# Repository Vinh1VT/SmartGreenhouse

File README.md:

# Mr Gardener - Serre Connectée

Ce dépôt contient les sources utilisée dans le projet Mr. Gardener, réalisé en 2026 pour la formation Electronique-Informatique d'année 4 à Polytech Sorbonne.

Ce document n'est qu'une courte description du projet, une documentation plus détaillé peut être trouvée [ici](https://github.com/Vinh1VT/SmartGreenhouse/blob/main/Mr.Gardener%20-%20SmartGreenHouse%20-%20User%20Guide.pdf)

##  Objectifs du projet

L'objectif principal est de concevoir un système autonome de mesures et de commandes pour la serre de l'école, sur le campus St Cyr l'école.
Le systême à donc comme caractéristique : 

- **Mesures Environnementale** : Acquisition de données environnementales (Humidité, température, luminosité...) pour la serre et son puits canadien
- **Basse Consommation** : Le projet fonctionne quasi entièrement sur batterie, et grâce à un rechargement par panneau solaire est en permanence autonome
- **IA Embarquée** : Proof of concept d'une détection locale de panne du ventilateur de la serre, via une IA de classification Edge Impulse
- **Collecte et visualisation des données** : Collecte, traitement et visualisation des données, via The Things Network, InfluxDB et Grafana
- **Contrôle du ventilateur** : Prototype d'une contrôleur I2C pour le ventilateur du puits canadien de la serre. Va être remplacé par un système plus robuste

##  Structure du dépôt

Les dossiers de ce dépôt contiennent les élément suivants :

*  **`Iot_PCB/`** : Projets KiCad (schémas et routages) pour la carte mère et les contrôleurs de ventilateurs
*  **`code_esp32_WROOM_32E/`** : Firmware principal (ESP32) gérant la lecture des capteurs, la logique de commande et la connectivité LoRa
*  **`nano_AI/`** : Modèles d'intelligence artificielle et code d'inférence (Edge Impulse) tournant sur l'Arduino Nano
*  **`Server/`** : Dashboard Grafana, Script Python de liaison TTN<->InfluxDB et Parser TTN

## Auteurs : 
- Vinh VO TUAN
- Fallou CORDELETTE
- Quentin LE VOURC'H
- Yanis RAHOUI
- Taha OUERFILI

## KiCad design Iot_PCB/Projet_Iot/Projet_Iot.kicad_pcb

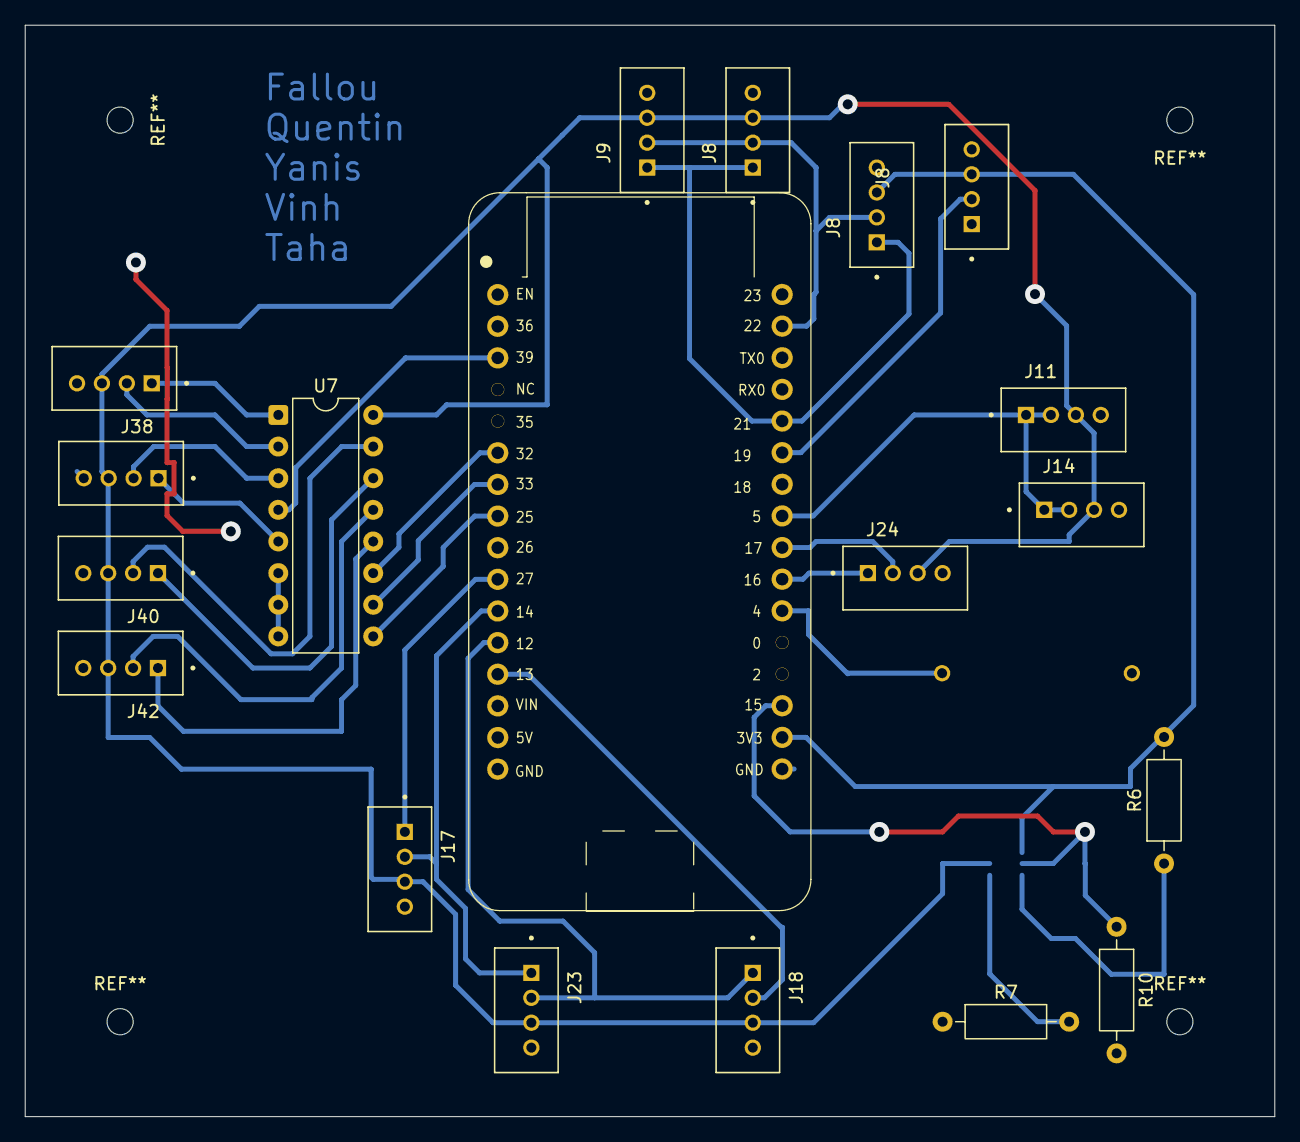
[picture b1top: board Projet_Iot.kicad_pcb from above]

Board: 2 copper layers, 100.3 x 87.6 mm, 20 parts (1 on the bottom side), 28 nets.

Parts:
J8, J8#2, J8#3, J9, J11, J14, J17, J18, J23, J24, J36, J38, J40, J42: 110990030; SEEED_110990030
R6: 1000; R_Axial_DIN0207_L6.3mm_D2.5mm_P10.16mm_Horizontal
R7: 100; R_Axial_DIN0207_L6.3mm_D2.5mm_P10.16mm_Horizontal
R10: 4700; R_Axial_DIN0207_L6.3mm_D2.5mm_P10.16mm_Horizontal
U6: uPesy_ESP32_Wroom_Low_Power_DevKit
U7: mx8v1_74LS151; DIP-16_W7.62mm
U11: FDC6326L; SOT95P280X110-6N

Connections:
/1_Wire: J11.1, J11.2, J14.1, J14.2, U6.24 (GPIO5)
/3v3: J8#3.3, J9.3, J11.3, J14.3, J17.3, J18.3, J23.3, J24.3, J36.3, J38.3, J40.3, J42.3, U7.16 (VCC), U11.2 (VOUT,C1_2)
/3v3_ESP: J8.3, J8#2.3, R6.2, U6.31 (3V3), U11.4 (VIN,R1)
/ADC1_S0: U6.6 (GPIO32), U7.11 (S0)
/ADC1_S1: U6.7 (GPIO33), U7.10 (S1)
/ADC1_S2: U6.8 (GPIO25), U7.9 (S2)
/ADC2: U6.3 (GPIO39), U7.4 (I0)
/Enable_LS: R10.1, U6.30 (GPIO15), U11.5 (ON/OFF)
/GND: J8.4, J8#2.4, J8#3.4, J9.4, J11.4, J14.4, J17.4, J18.4, J23.4, J24.4, J36.4, J38.4, J40.4, J42.4, R7.1, R10.2, U6.32 (GND), U7.6 (~Z), U7.7 (~E), U7.8 (GND)
/Grove1-1: J17.1, U6.10 (GPIO27)
/Grove1-2: J17.2, J23.1, U6.11 (GPIO14)
/Grove2-3: J18.1, J23.2, U6.12 (GPIO12)
/Grove3-3: J18.2, U6.13 (GPIO13)
/Mux8v1_capt_hum1/Hum0: J36.1, U7.5 (Z)
/Mux8v1_capt_hum1/Hum1: J36.2, U7.3 (I1)
/Mux8v1_capt_hum1/Hum2: J38.2, U7.2 (I2)
/Mux8v1_capt_hum1/Hum3: J38.1, U7.1 (I3)
/Mux8v1_capt_hum1/Hum4: J40.2, U7.15 (I4)
/Mux8v1_capt_hum1/Hum5: J40.1, U7.14 (I5)
/Mux8v1_capt_hum1/Hum6: J42.2, U7.13 (I6)
/Mux8v1_capt_hum1/Hum7: J42.1, U7.12 (I7)
/SDA: J8.1, J8#3.1, J9.1, U6.21 (GPIO21)
/SDL: J8.2, J8#3.2, J9.2, U6.18 (GPIO22)
/interrupt_ia: J8#2.2, U6.22 (GPIO19)
unnamed: J24.1, U6.26 (GPIO16)
unnamed: J24.2, U6.25 (GPIO17)
unnamed: R6.1, U11.6 (R1,C1)
unnamed: R7.2, U11.1 (R2)

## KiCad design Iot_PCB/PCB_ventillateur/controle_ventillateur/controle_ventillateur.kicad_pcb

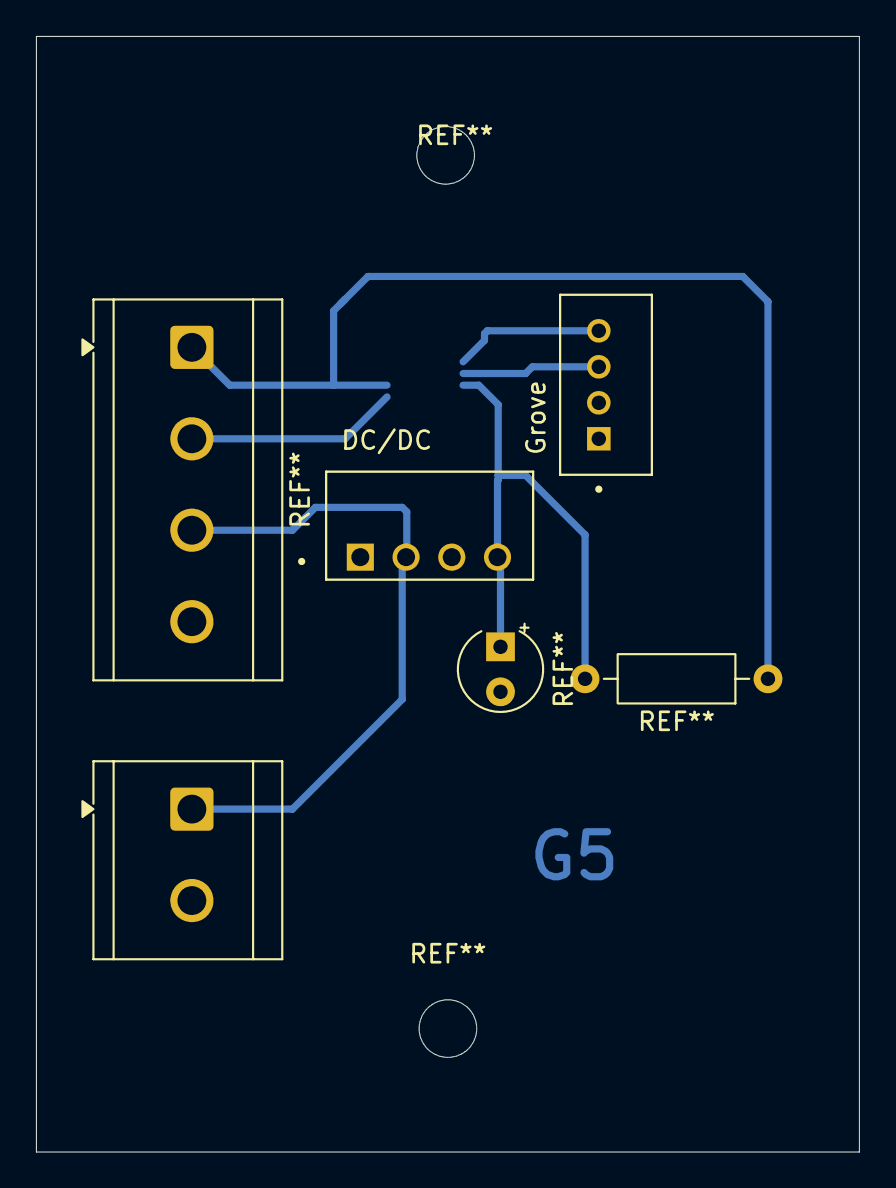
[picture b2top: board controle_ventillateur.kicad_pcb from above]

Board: 2 copper layers, 45.7 x 62.0 mm, 3 parts (1 on the bottom side), 4 nets.

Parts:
DC/DC: CONV_RFM-0505S
Grove: SEEED_110990030
U7: EMC2301-x-ACZL; MSOP-8_3x3mm_P0.65mm

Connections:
/GND: DC/DC.1, DC/DC.3, Grove.1, U7.4 (GND)
/SCL: Grove.3, U7.2 (SMCLK)
/SDA: Grove.4, U7.1 (SMDATA)
unnamed: DC/DC.4, U7.3 (VDD)

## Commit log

2026-02-18 build(server) : add docker-compose.yml
    Add docker compose file with nodered, grafana and influxdb configuration
2026-02-18 build(esp32) : add driver_UART header and c files
    add the start of files to use the UART module of the esp32, function init added
2026-02-18 build(esp32) : add code_esp32_WROOM_32E.ino
    add the start of an esp32 project
2026-02-18 fix(Serveur): update docker-compose.yml
2026-02-18 build(Server) : update gitignore and add nodered files to the git
2026-02-19 build(Server): Add dockerfiles for addons portability (nodered and grafana)
2026-02-19 build: Add readme
    Add a readme for using the server in it's current state
2026-02-19 build(Server) : add a description to the environments variables in example
2026-02-23 fix(Server) : Remove docker, we're not going to use it
2026-02-23 build(esp32) : add function write_UART to driver_UART
2026-02-23 build(esp32) : add functions to read from UART
    add function read_byte, read_bytes and read_until
2026-02-23 build(Server) : Add the start of the python script to bridge between ttn and the db
2026-02-23 build(Server) : Modified the example environment to be compatible with the python script
2026-02-23 fix(esp32) : correct problem that made the code impossible to compile
2026-02-23 build(esp32) : add function to command the LoRa module
2026-02-23 fix(esp32) : correct a forgotten typo
2026-02-23 fix(esp32) : remove a forgoten useless function call
2026-02-23 fix(esp32) : change a function to correct a problem
2026-02-23 test(esp32) : analog reading working, mux control is not tho
2026-02-24 build(Server) : add parser in the python script
2026-02-24 build(Server) : Add fan historic to the python script
2026-02-24 fix(esp32) : working mux with pins in define (i believe)
2026-02-24 fix(Server) : added the opening of .env in the python script
2026-02-24 fix(esp32) : gpios forced at 0 in the end of the function for energy purposes
2026-02-24 build(Server) : add a readme and lib files for using the local version of the pipeline
2026-02-24 build(esp32) : Add functions to read the temperature from ds18b20 sensors
2026-02-24 build(esp32) : add function to read temperature and humidity from one DHT22 sensor
2026-02-24 build(Kicad) : add the kicad files (schematic for now)
2026-02-24 fix(kicad) : update with the latest files
2026-02-25 Update(esp32) : fix multiple problems found during testing
2026-02-25 Update(esp32) : made a test code to test all other code in one file
2026-02-25 build(esp32) : add function to convert sensor data to ttn payload
2026-02-25 remplacement des grove lora par des vrais
2026-02-26 update 1-wire, pull_up i2c, switch load added but not configured yet (wait for test)
2026-03-02 build(esp32) : add the function to convert payload to hexstring
2026-03-02 fix(esp32): correct send LoRa function, to use MSGHEX
2026-03-02 adding grove to replace lora
2026-03-02 build(kicad): add a trace to every schematic
2026-03-02 test(esp32) : test a commit y'a r y'a r
2026-03-02 ijustwanttopull(esp32) : commit pour pouvoir pull rebase
2026-03-02 fix(esp32) : le capteur de lumiere I2C fonctionne quand soudé
2026-03-02 modif(esp32) ajout du driver pour le switch load et quelque changements autour
2026-03-02 build(kicad) : start PCB
2026-03-02 modif(esp32) : add function to support the new way of sending information
2026-03-02 modif(esp32) : add 2 temperature values
2026-03-02 new(esp32) : deep sleep
2026-03-05 pcb mis à jour
2026-03-05 update(ScriptPython) : update to add tags to the DB
2026-03-06 Update(Server) : Update script to use the choosen database format
2026-03-09 fix(esp32) : Correct deep sleep and load switch function
2026-03-09 modif(esp32) : change success condition of LoRa connection
2026-03-09 modif(esp32) : make the code a little clearer
2026-03-09 modif(esp32) : forgot to include this file in the former commit
2026-03-09 modif(esp32) : update the reading send by the payload
2026-03-09 modif(esp32) : update to comply with new payload
2026-03-09 build(esp32) : add the beginning of main loop
2026-03-09 patch(Esp32) : remove the fan data from the uplink structure
2026-03-09 modif(esp32) : fix multiple issues, now work on card
2026-03-09 modif(esp32) : coorect some names
2026-03-09 ajout driver gaz
2026-03-09 working(esp32) : je fait l'i2c des gaz
2026-03-09 drivers(esp32) : les drivers sont normalement complet, plus qu'a integrer sur le main
2026-03-09 modif(esp32) : change a bunch of thing, now work with the load switch
2026-03-09 modif(esp32) : fix the header name
2026-03-09 modif(esp32) : add reading of lux and ambiant hum and temp
2026-03-09 pcb and schematic up to date
2026-03-09 pcb upgraded, adding the forgotten capacitor
2026-03-10 build(AI) : example code for the AI working
2026-03-10 build(AI) : add the I2C slave code
2026-03-10 modif(esp32) : replace the read sensors to the BH1745
2026-03-10 modif(esp32) : fix an issue where the message did not have time to get sent
2026-03-10 modif(esp32) : fix a probleme of operation priority
2026-03-10 modif(esp32) : implement the changes made previously
2026-03-10 modif(esp32) : change the init function to get rid of the while loop
2026-03-10 modif(esp 32) : move the sleep time to a define constant
2026-03-12 final version of pcb
2026-03-14 commit pour pull
2026-03-14 new(esp32) driver IA
2026-03-16 build(Server) :fix the python script
2026-03-24 build(Server) : downlink ajouté
2026-03-24 fix(Server) : delete unused variables
2026-03-24 fix(Server) : put back unused variables (they were important)
2026-03-29 build(Server) : i literally built a fastapi server to bypass influxDB requests
2026-03-30 pcb final version for both the gloabl projet and for the ventillator
2026-03-31 correction pcb final
2026-03-31 je dois me depecher
2026-03-31 correctif due a une mauvaise manip
2026-03-31 build(Script):Script python fixed
2026-03-31 Update(Script) : change the comments
2026-04-03 modif(esp32) : fix i2c problem from luminosity captor (thanks to yanis) and add a limit to the downlink reader to prevent error
2026-04-03 modif(esp32) : add possibility to monitor battery charge (currently sent to tty in pplace of the 02, will be changed later)
2026-04-05 build(IA):replaced the AI, and put the correct code to communicate with main board
2026-04-06 modif(esp32) : add possibility to get data from AI card
2026-04-07 final sprint
2026-04-08 modif(esp32) : currently flashed on the card (doesn't include downlink)
2026-04-08 modif(esp32) : attempt to read downlink message
2026-04-08 modif(esp32) : add a default value to the downlink buffer
2026-04-13 modif(Server) : fix du serveur python et de la carte IA
2026-04-21 docs: add user guide
2026-04-21 Feat(TTN) : Add TTN Parser to the repo
2026-04-21 Feat(Grafana) : Add grafana dashboard to the repo
